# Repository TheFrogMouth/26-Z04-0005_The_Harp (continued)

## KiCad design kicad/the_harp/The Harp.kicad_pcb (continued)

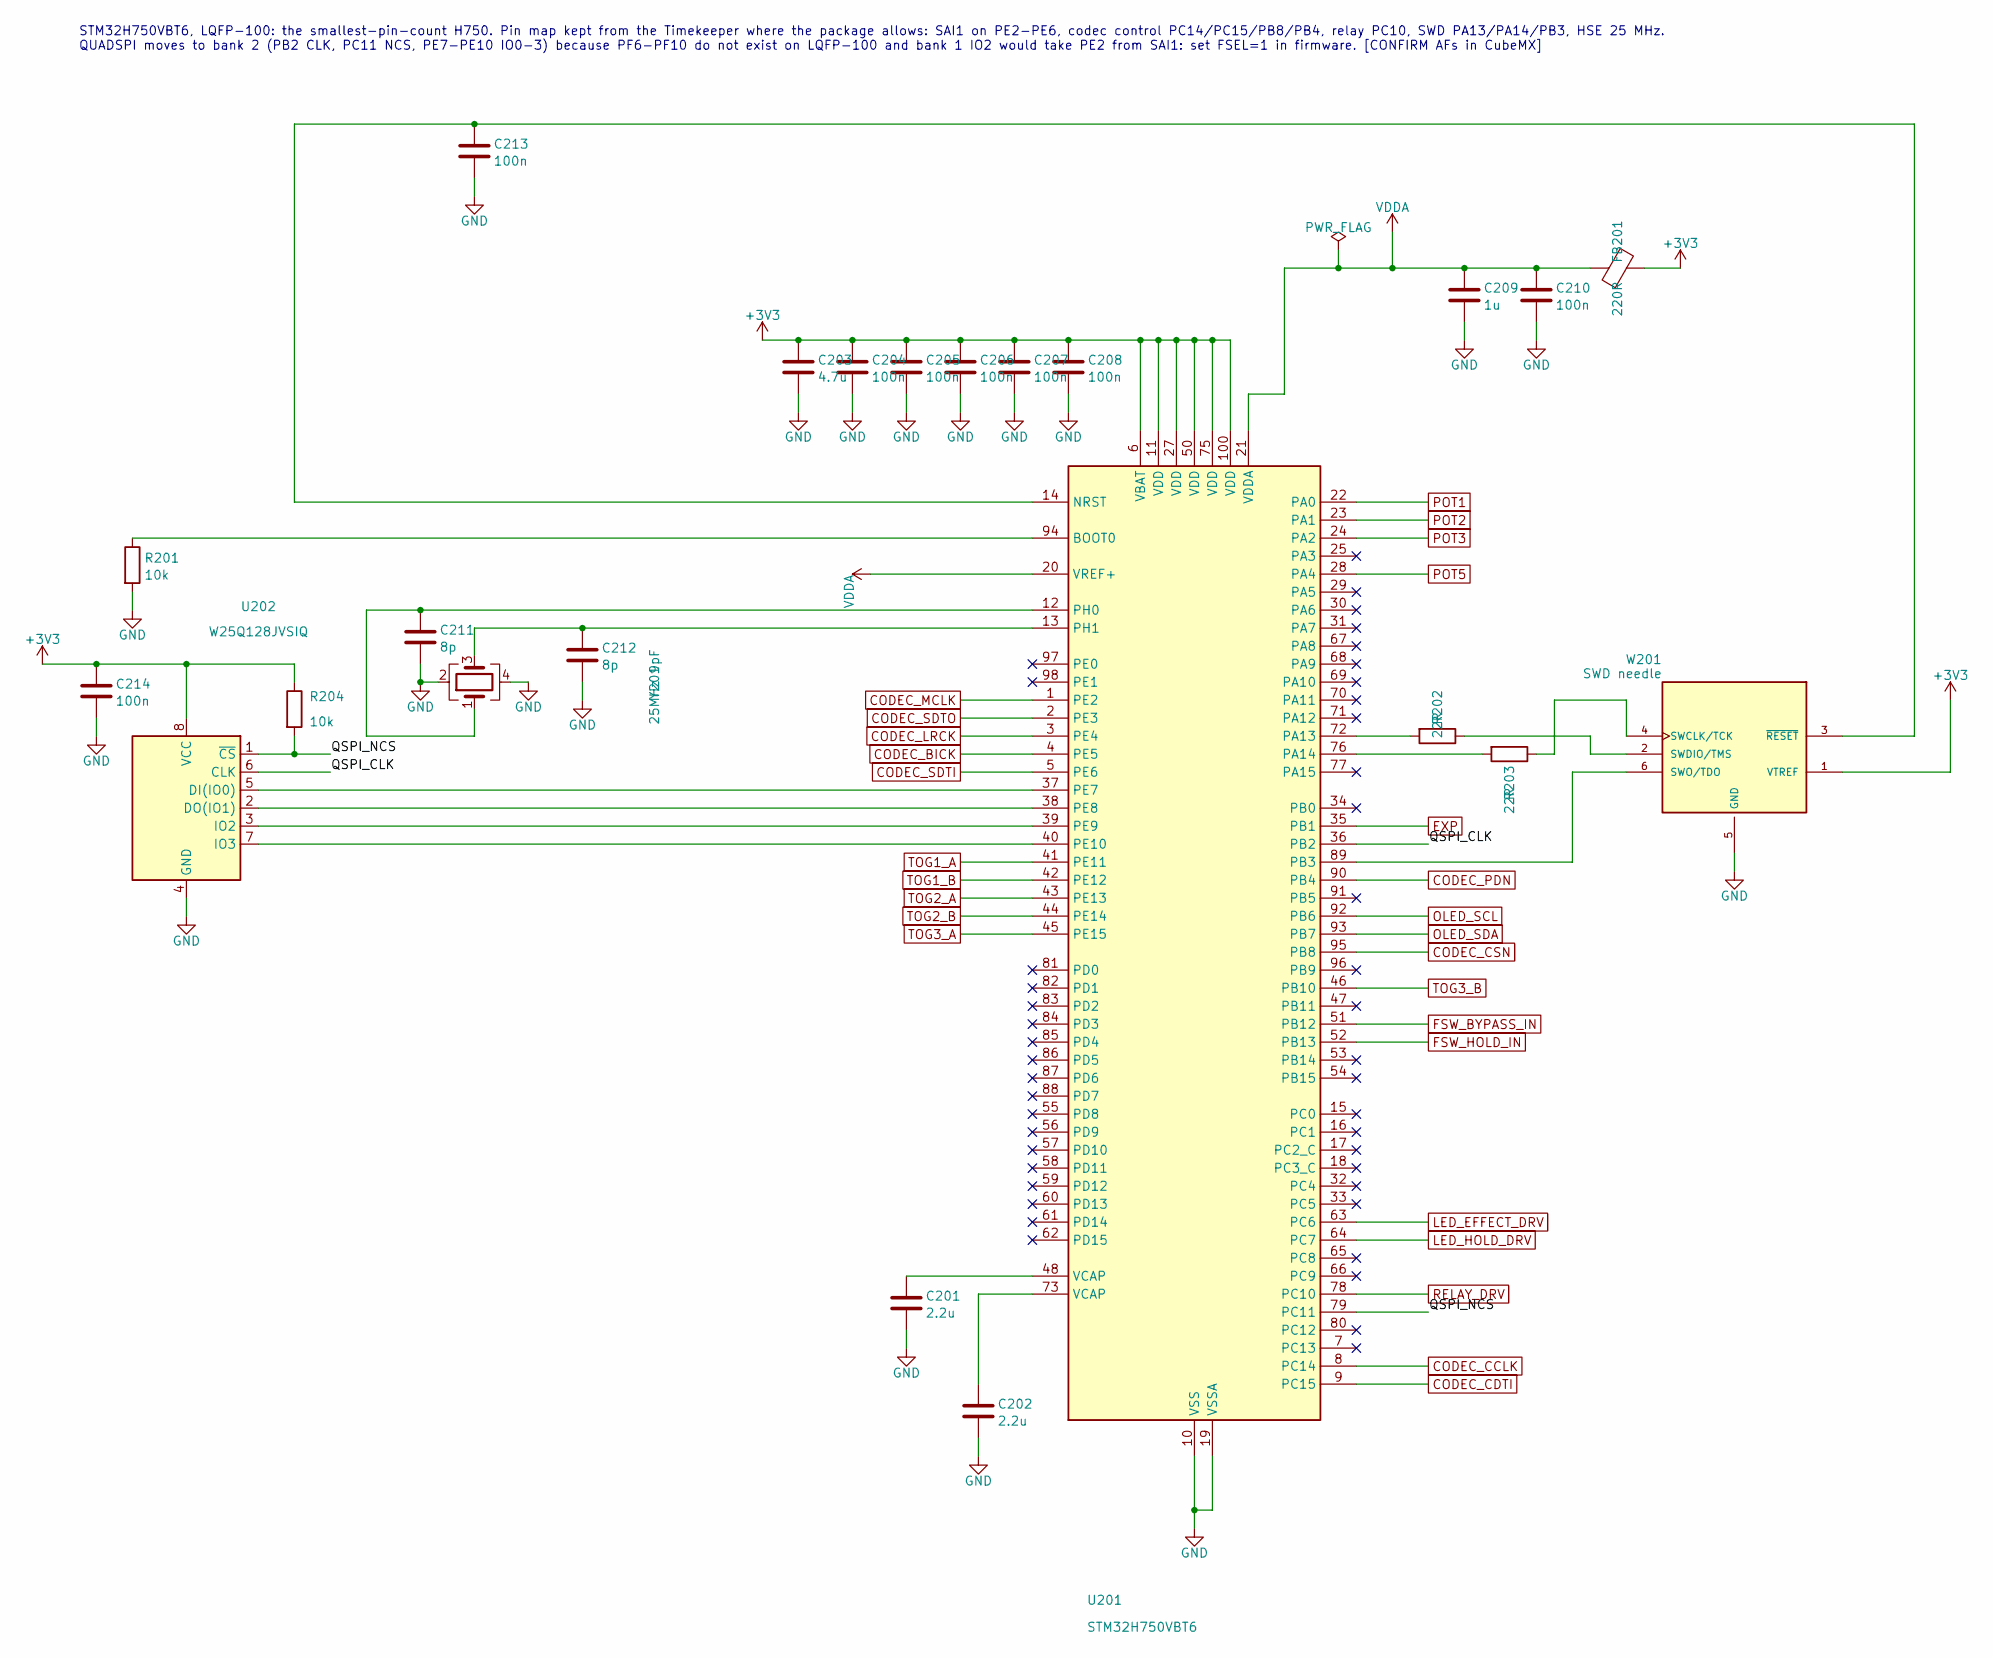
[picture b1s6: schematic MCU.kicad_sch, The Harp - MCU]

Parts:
C201, C202: 2.2u; C_0603_1608Metric
C203: 4.7u; C_0805_2012Metric
C204, C205, C206, C207, C208, C210, C213, C214: 100n; C_0603_1608Metric
C209: 1u; C_0603_1608Metric
C211, C212: 8p; C_0603_1608Metric
FB201: 220R; L_0603_1608Metric
R201, R204: 10k; R_0603_1608Metric
R202, R203: 22R; R_0603_1608Metric
U201: STM32H750VBT6; LQFP-100_14x14mm_P0.5mm; Mfg Part # STM32H750VBT6
U202: W25Q128JVSIQ; SOIC-8_5.23x5.23mm_P1.27mm; Mfg Part # W25Q128JVSIQ
W201: SWD needle; SEGGER_8.06.05_6-PIN_NEEDLE_ADAPTER
Y201: 25MHz 9pF; Crystal_SMD_2016-4Pin_2.0x1.6mm

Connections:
+3V3: C203.1, C204.1, C205.1, C206.1, C207.1, C208.1, C214.1, FB201.1, R204.1, U201.6 (VBAT), U201.11 (VDD), U201.27 (VDD), U201.50 (VDD), U201.75 (VDD), U201.100 (VDD), U202.8 (VCC), W201.1 (VTREF); also elsewhere on the board
/MCU/QSPI_CLK: U201.36 (PB2), U202.6 (CLK)
/MCU/QSPI_NCS: R204.2, U201.79 (PC11), U202.1 (~CS)
CODEC_BICK: U201.4 (PE5); also elsewhere on the board
CODEC_CCLK: U201.8 (PC14); also elsewhere on the board
CODEC_CDTI: U201.9 (PC15); also elsewhere on the board
CODEC_CSN: U201.95 (PB8); also elsewhere on the board
CODEC_LRCK: U201.3 (PE4); also elsewhere on the board
CODEC_MCLK: U201.1 (PE2); also elsewhere on the board
CODEC_PDN: U201.90 (PB4); also elsewhere on the board
CODEC_SDTI: U201.5 (PE6); also elsewhere on the board
CODEC_SDTO: U201.2 (PE3); also elsewhere on the board
EXP: U201.35 (PB1); also elsewhere on the board
FSW_BYPASS_IN: U201.51 (PB12); also elsewhere on the board
FSW_HOLD_IN: U201.52 (PB13); also elsewhere on the board
GND: C201.2, C202.2, C203.2, C204.2, C205.2, C206.2, C207.2, C208.2, C209.2, C210.2, C211.2, C212.2, C213.2, C214.2, R201.2, U201.10 (VSS), U201.19 (VSSA), U201.26 (VSS), U201.49 (VSS), U201.74 (VSS), U201.99 (VSS), U202.4 (GND), W201.5 (GND), Y201.2, Y201.4; also elsewhere on the board
LED_EFFECT_DRV: U201.63 (PC6); also elsewhere on the board
LED_HOLD_DRV: U201.64 (PC7); also elsewhere on the board
unnamed: C201.1, U201.48 (VCAP)
unnamed: C202.1, U201.73 (VCAP)
unnamed: R201.1, U201.94 (BOOT0)
unnamed: C213.1, U201.14 (NRST), W201.3 (~RESET)
unnamed: R202.2, U201.72 (PA13)
unnamed: R203.2, U201.76 (PA14)
unnamed: U201.89 (PB3), W201.6 (SWO/TDO)
unnamed: U201.37 (PE7), U202.5 (DI(IO0))
unnamed: U201.38 (PE8), U202.2 (DO(IO1))
unnamed: U201.39 (PE9), U202.3 (IO2)
unnamed: U201.40 (PE10), U202.7 (IO3)
unnamed: C211.1, U201.12 (PH0), Y201.1
unnamed: C212.1, U201.13 (PH1), Y201.3
unnamed: R203.1, W201.4 (SWCLK/TCK)
unnamed: R202.1, W201.2 (SWDIO/TMS)
OLED_SCL: U201.92 (PB6); also elsewhere on the board
OLED_SDA: U201.93 (PB7); also elsewhere on the board
POT1: U201.22 (PA0); also elsewhere on the board
POT2: U201.23 (PA1); also elsewhere on the board
POT3: U201.24 (PA2); also elsewhere on the board
POT5: U201.28 (PA4); also elsewhere on the board
RELAY_DRV: U201.78 (PC10); also elsewhere on the board
TOG1_A: U201.41 (PE11); also elsewhere on the board
TOG1_B: U201.42 (PE12); also elsewhere on the board
TOG2_A: U201.43 (PE13); also elsewhere on the board
TOG2_B: U201.44 (PE14); also elsewhere on the board
TOG3_A: U201.45 (PE15); also elsewhere on the board
TOG3_B: U201.46 (PB10); also elsewhere on the board
VDDA: C209.1, C210.1, FB201.2, U201.20 (VREF+), U201.21 (VDDA)

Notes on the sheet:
STM32H750VBT6, LQFP-100: the smallest-pin-count H750. Pin map kept from the Timekeeper where the package allows: SAI1 on PE2-PE6, codec control PC14/PC15/PB8/PB4, relay PC10, SWD PA13/PA14/PB3, HSE 25 MHz. QUADSPI moves to bank 2 (PB2 CLK, PC11 NCS, PE7-PE10 IO0-3) because PF6-PF10 do not exist on 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

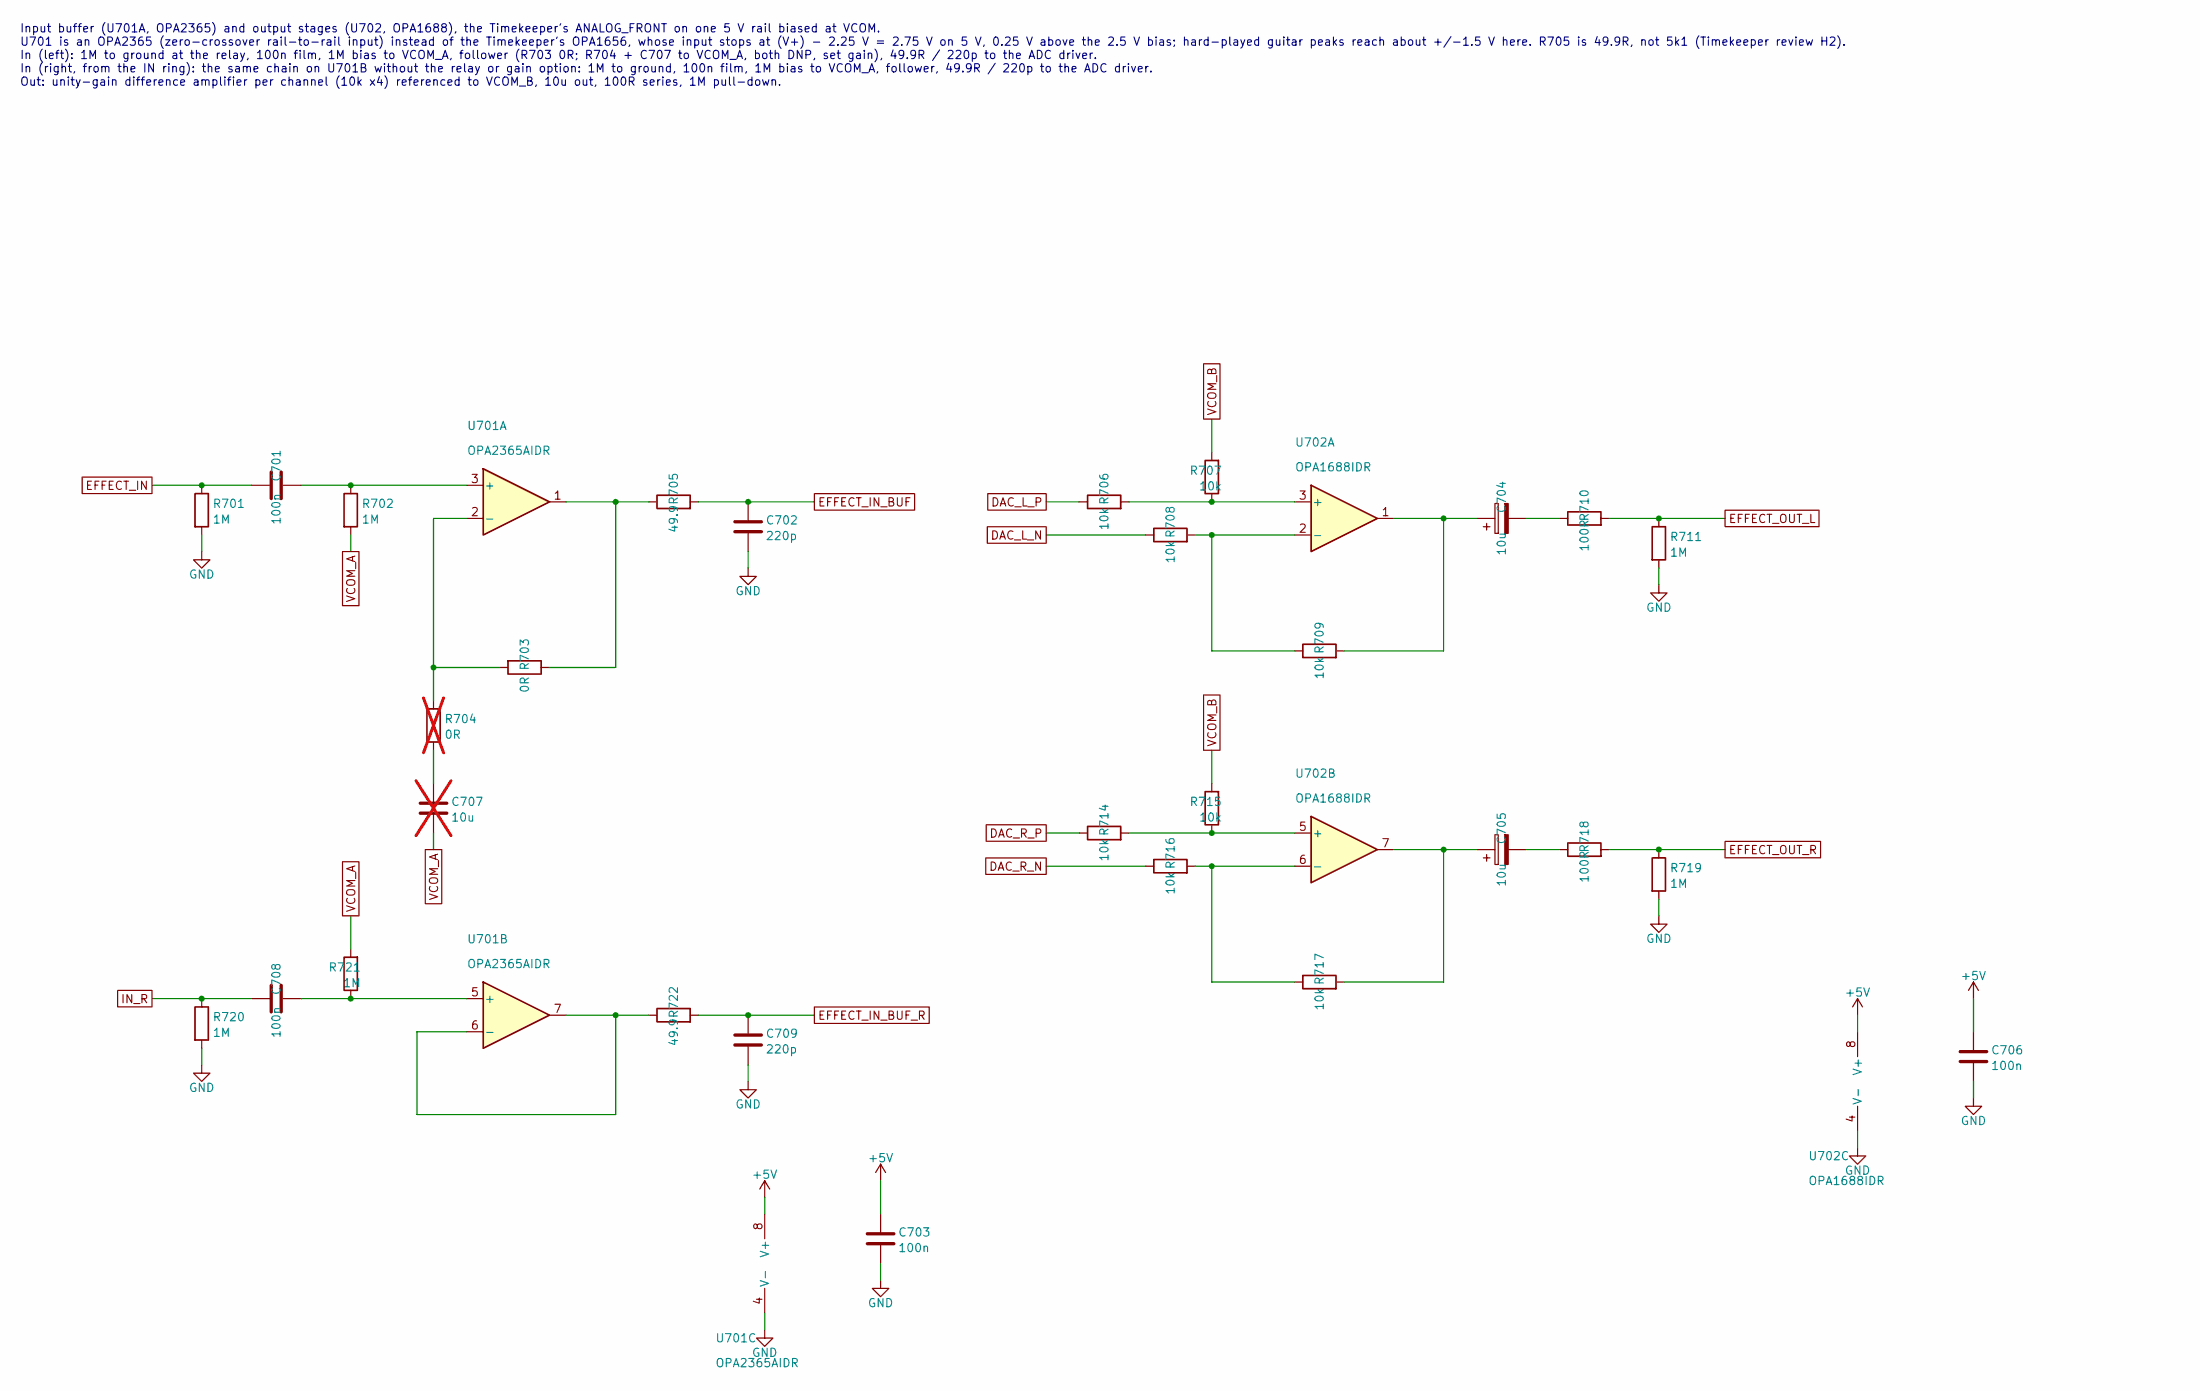
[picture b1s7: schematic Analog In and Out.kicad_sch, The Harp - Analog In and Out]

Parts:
C701, C708: 100n; C_1206_3216Metric
C702, C709: 220p; C_0603_1608Metric
C703, C706: 100n; C_0603_1608Metric
C704, C705: 10u; CP_EIA-3216-12_Kemet-S
C707: 10u; C_0805_2012Metric; not fitted
R701, R702, R711, R719, R720, R721: 1M; R_0603_1608Metric
R703: 0R; R_0603_1608Metric
R704: 0R; R_0603_1608Metric; not fitted
R705, R722: 49.9; R_0603_1608Metric
R706, R707, R708, R709, R714, R715, R716, R717: 10k; R_0603_1608Metric
R710, R718: 100R; R_0603_1608Metric
U701: OPA2365AIDR; SOIC-8_3.9x4.9mm_P1.27mm; Mfg Part # OPA2365AIDR
U702: OPA1688IDR; SOIC-8_3.9x4.9mm_P1.27mm; Mfg Part # OPA1688IDR

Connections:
+5V: C703.1, C706.1, U701.8 (V+), U702.8 (V+); also elsewhere on the board
DAC_L_N: R708.1; also elsewhere on the board
DAC_L_P: R706.1; also elsewhere on the board
DAC_R_N: R716.1; also elsewhere on the board
DAC_R_P: R714.1; also elsewhere on the board
EFFECT_IN: C701.1, R701.1; also elsewhere on the board
EFFECT_IN_BUF: C702.1, R705.2; also elsewhere on the board
EFFECT_IN_BUF_R: C709.1, R722.2; also elsewhere on the board
EFFECT_OUT_L: R710.2, R711.1; also elsewhere on the board
EFFECT_OUT_R: R718.2, R719.1; also elsewhere on the board
GND: C702.2, C703.2, C706.2, C709.2, R701.2, R711.2, R719.2, R720.2, U701.4 (V-), U702.4 (V-); also elsewhere on the board
IN_R: C708.1, R720.1; also elsewhere on the board
unnamed: C704.1, R709.2, U702.1
unnamed: C704.2, R710.1
unnamed: C705.1, R717.2, U702.7
unnamed: C705.2, R718.1
unnamed: C707.1, R704.2
unnamed: R703.1, R705.1, U701.1
unnamed: C701.2, R702.1, U701.3 (+)
unnamed: R703.2, R704.1, U701.2 (-)
unnamed: C708.2, R721.1, U701.5 (+)
unnamed: R722.1, U701.6 (-), U701.7
unnamed: R706.2, R707.1, U702.3 (+)
unnamed: R708.2, R709.1, U702.2 (-)
unnamed: R714.2, R715.1, U702.5 (+)
unnamed: R716.2, R717.1, U702.6 (-)
VCOM_A: C707.2, R702.2, R721.2; also elsewhere on the board
VCOM_B: R707.2, R715.2; also elsewhere on the board

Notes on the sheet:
Input buffer (U701A, OPA2365) and output stages (U702, OPA1688), the Timekeeper's ANALOG_FRONT on one 5 V rail biased at VCOM. U701 is an OPA2365 (zero-crossover rail-to-rail input) instead of the Timekeeper's OPA1656, whose input stops at (V+) - 2.25 V = 2.75 V on 5 V, 0.25 V above the 2.5 V bias;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

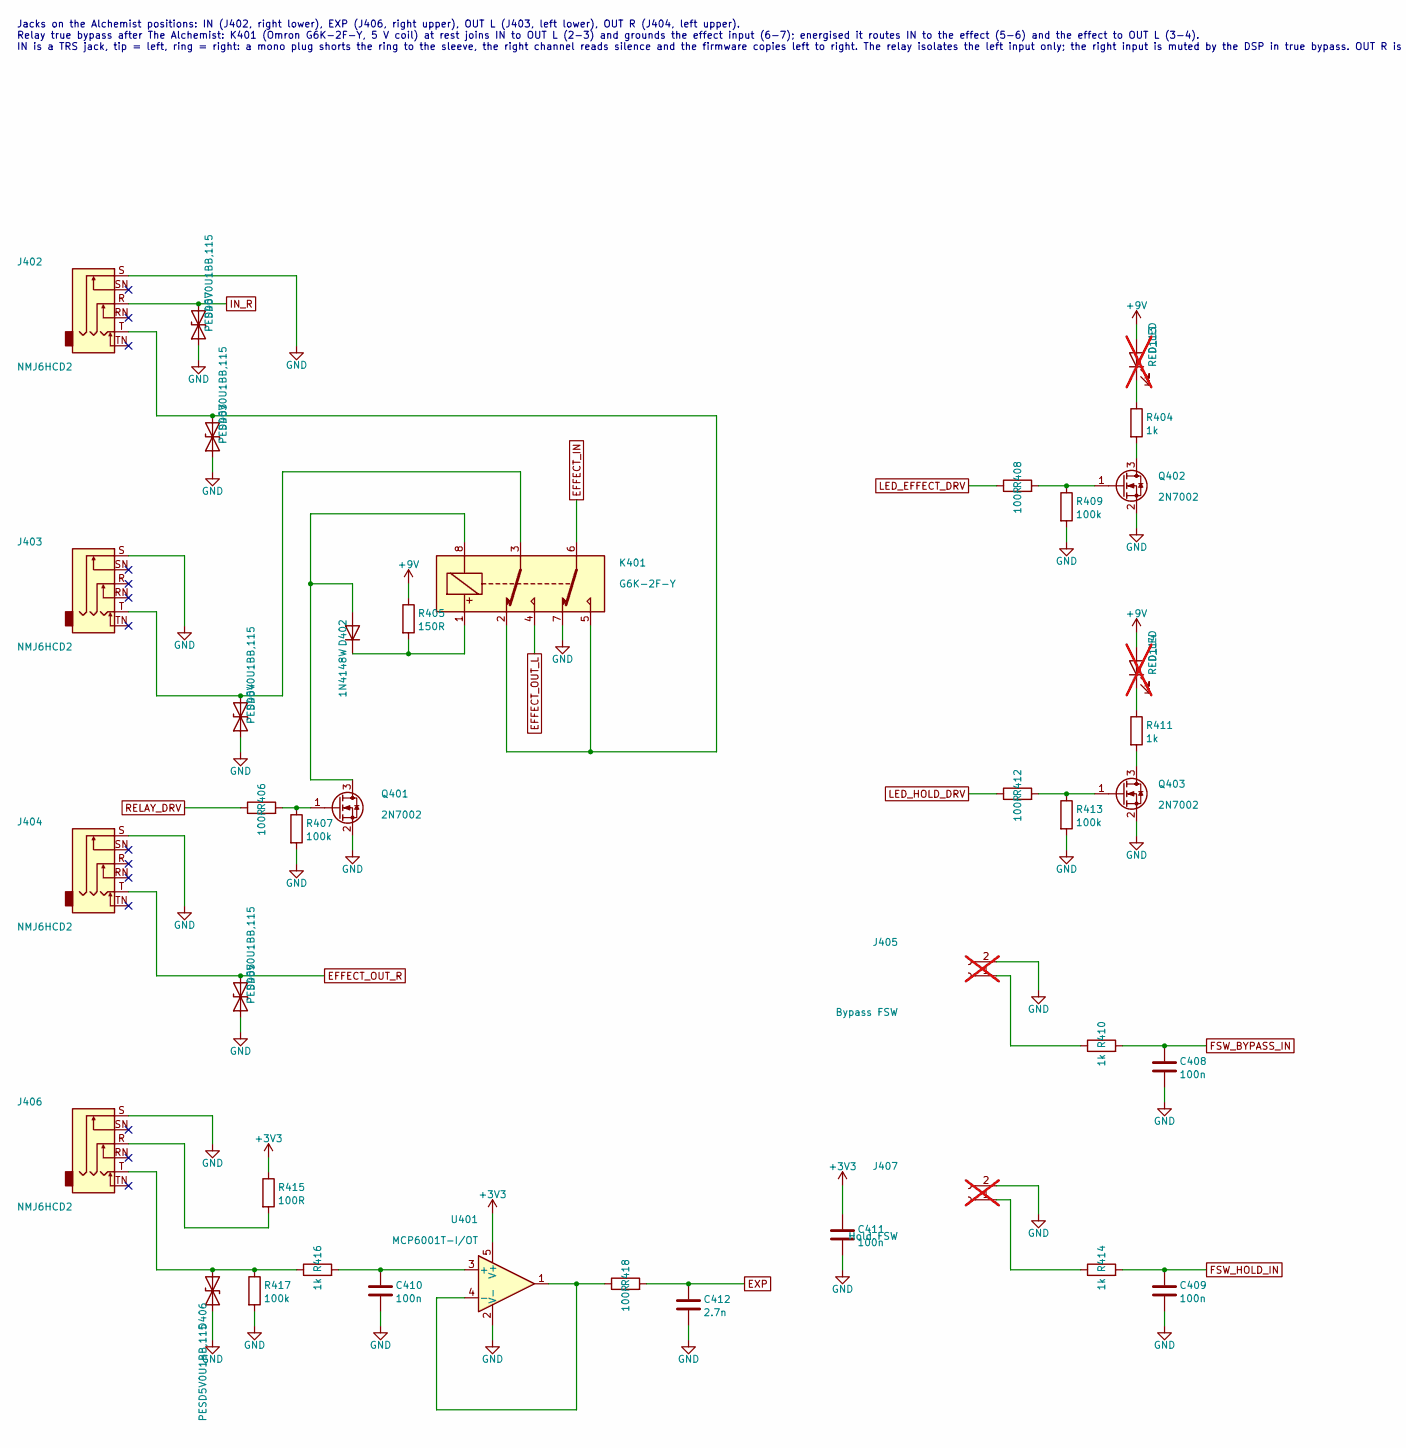
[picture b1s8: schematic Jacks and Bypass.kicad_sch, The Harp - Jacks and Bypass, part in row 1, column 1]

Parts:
C408, C409: 100n; C_0603_1608Metric; Mfg Part # CC0603KRX7R9BB104; LCSC C14663
C410, C411: 100n; C_0603_1608Metric
C412: 2.7n; C_0603_1608Metric
D113, D114: RED_LED; LED_D3.0mm; Mfg Part # WP710A10ID; not fitted
D402: 1N4148W; D_SOD-123; Mfg Part # 1N4148W-7-F; LCSC C7420318
D403, D404, D405, D406, D407: PESD5V0U1BB,115; D_SOD-523; Mfg Part # PESD5V0U1BB,115
J402, J403, J404, J406: NMJ6HCD2; Jack_6.35mm_Neutrik_NMJ6HCD2_Horizontal; Mfg Part # NMJ6HCD2; LCSC C309277
J405: Bypass FSW; R_2816_7142Metric_Pad3.20x4.45mm_HandSolder; not fitted
J407: Hold FSW; R_2816_7142Metric_Pad3.20x4.45mm_HandSolder; not fitted
K401: G6K-2F-Y; Relay_DPDT_Omron_G6K-2F-Y; Mfg Part # G6K-2F-Y DC5; LCSC C2982926
Q401, Q402, Q403: 2N7002; SOT-23; Mfg Part # 2N7002LT1G; LCSC C7420321
R404, R410, R411, R414: 1k; R_0805_2012Metric; Mfg Part # AC0805FR-071KL; LCSC C17513
R405: 150R; R_1206_3216Metric; Mfg Part # RC1206FR-07150RL; LCSC C17917
R406, R408, R412: 100R; R_0805_2012Metric; Mfg Part # AC0805FR-07100RL; LCSC C7468571
R407, R409, R413: 100k; R_0805_2012Metric; Mfg Part # AC0805FR-07100KL; LCSC C149504
R415, R418: 100R; R_0603_1608Metric
R416: 1k; R_0603_1608Metric
R417: 100k; R_0603_1608Metric
U401: MCP6001T-I/OT; SOT-23-5; Mfg Part # MCP6001T-I/OT

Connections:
+3V3: C411.1, R415.1, U401.5 (V+); also elsewhere on the board
+9V: D113.2 (A), D114.2 (A), R405.1; also elsewhere on the board
EFFECT_IN: K401.6; also elsewhere on the board
EFFECT_OUT_L: K401.4; also elsewhere on the board
EFFECT_OUT_R: D405.2 (A2), J404.T; also elsewhere on the board
EXP: C412.1, R418.2; also elsewhere on the board
FSW_BYPASS_IN: C408.1, R410.2; also elsewhere on the board
FSW_HOLD_IN: C409.1, R414.2; also elsewhere on the board
GND: C408.2, C409.2, C410.2, C411.2, C412.2, D403.1 (A1), D404.1 (A1), D405.1 (A1), D406.1 (A1), D407.1 (A1), J402.S, J403.S, J404.S, J405.2, J406.S, J407.2, K401.7, Q401.2 (S), Q402.2 (S), Q403.2 (S), R407.2, R409.2, R413.2, R417.2, U401.2 (V-); also elsewhere on the board
IN_R: D407.2 (A2), J402.R; also elsewhere on the board
LED_EFFECT_DRV: R408.1; also elsewhere on the board
LED_HOLD_DRV: R412.1; also elsewhere on the board
unnamed: D113.1 (K), R404.1
unnamed: D114.1 (K), R411.1
unnamed: D402.2 (A), K401.8, Q401.3 (D)
unnamed: D402.1 (K), K401.1, R405.2
unnamed: D403.2 (A2), J402.T, K401.2, K401.5
unnamed: D404.2 (A2), J403.T, K401.3
unnamed: D406.2 (A2), J406.T, R416.1, R417.1
unnamed: J405.1, R410.1
unnamed: J406.R, R415.2
unnamed: J407.1, R414.1
unnamed: Q401.1 (G), R406.2, R407.1
unnamed: Q402.3 (D), R404.2
unnamed: Q402.1 (G), R408.2, R409.1
unnamed: Q403.3 (D), R411.2
unnamed: Q403.1 (G), R412.2, R413.1
unnamed: C410.1, R416.2, U401.3 (+)
unnamed: R418.1, U401.1, U401.4 (-)
RELAY_DRV: R406.1; also elsewhere on the board

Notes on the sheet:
Jacks on the Alchemist positions: IN (J402, right lower), EXP (J406, right upper), OUT L (J403, left lower), OUT R (J404, left upper). Relay true bypass after The Alchemist: K401 (Omron G6K-2F-Y, 5 V coil) at rest joins IN to OUT L (2-3) and grounds the effect input (6-7); energised it routes IN to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

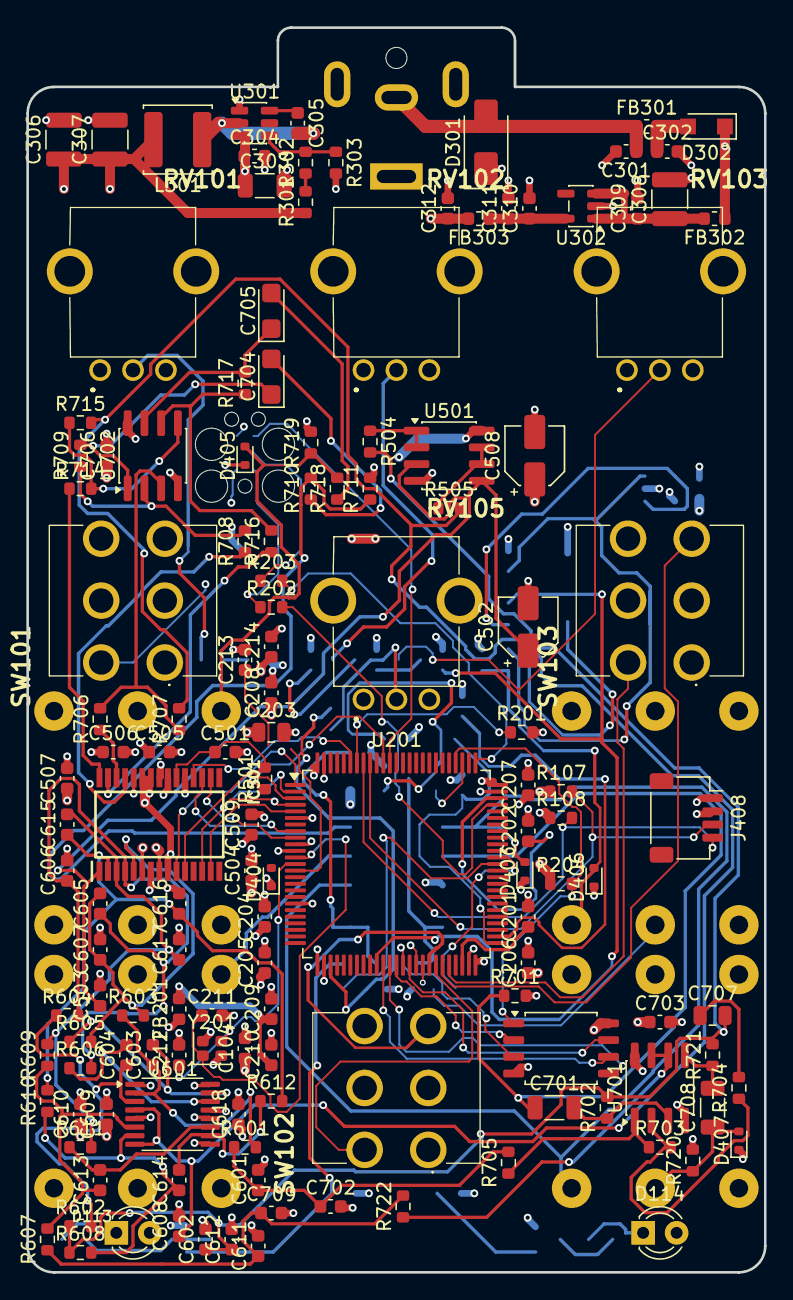
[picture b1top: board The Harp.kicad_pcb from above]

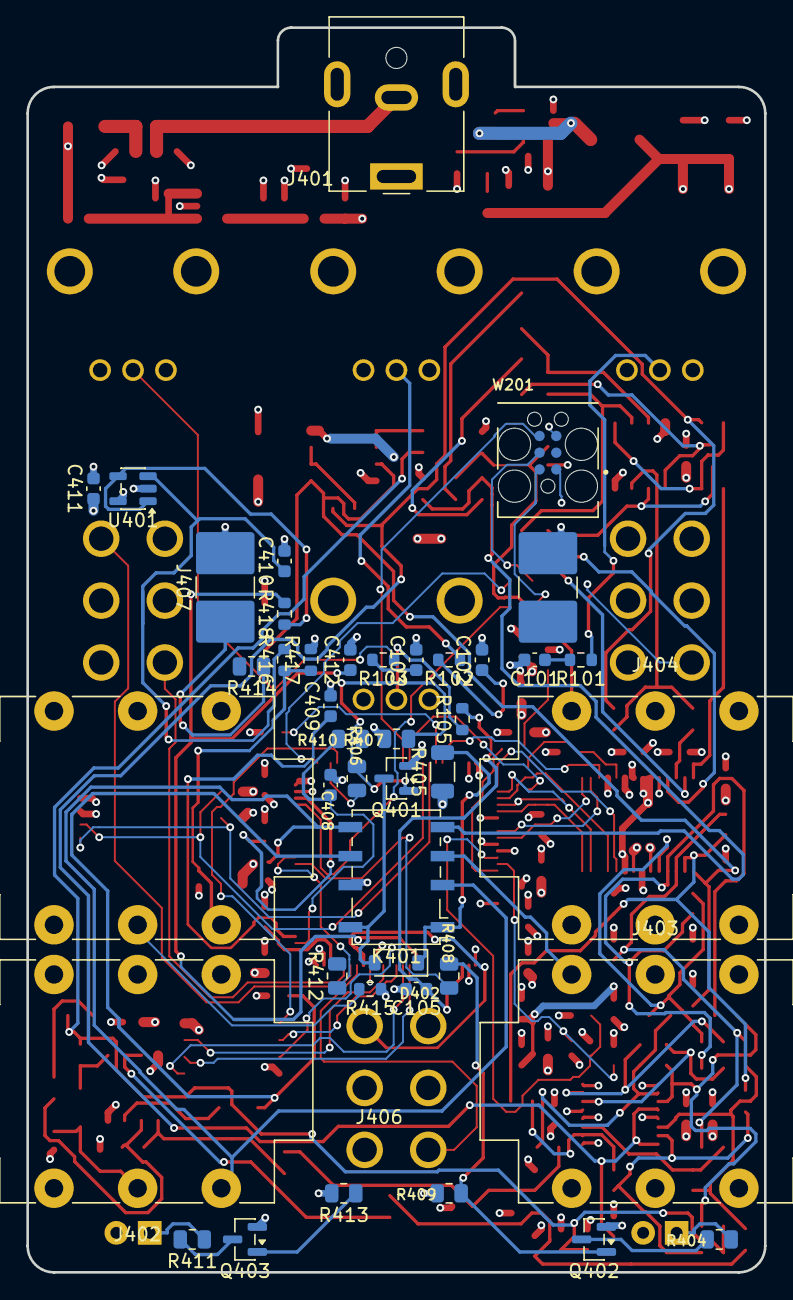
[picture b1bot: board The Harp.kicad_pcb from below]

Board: 4 copper layers, 56.0 x 94.5 mm, 181 parts (42 on the bottom side), 120 nets.

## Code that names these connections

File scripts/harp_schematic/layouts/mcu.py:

"""MCU: STM32H750VBT6 with its supplies, HSE crystal, reset and boot, SWD needle pads and the W25Q128 QSPI flash.

Two nets get local labels: QSPI_CLK (PB2, right side) and QSPI_NCS (PC11, right side) go to the flash on the
left; the flash sits on the left so its four IO lines run straight into PE7-PE10."""
from layouts.common import u, U, shunt, series

NOTES = ['C', 'Cs', 'D', 'Ds', 'E', 'F', 'Fs', 'G', 'Gs', 'A', 'As', 'B']
LEFT = {'PE2': 'CODEC_MCLK', 'PE3': 'CODEC_SDTO', 'PE4': 'CODEC_LRCK', 'PE5': 'CODEC_BICK', 'PE6': 'CODEC_SDTI',
        'PE7': None, 'PE8': None, 'PE9': None, 'PE10': None,
        'PE11': 'TOG1_A', 'PE12': 'TOG1_B', 'PE13': 'TOG2_A', 'PE14': 'TOG2_B', 'PE15': 'TOG3_A'}
RIGHT = {'PA0': 'POT1', 'PA1': 'POT2', 'PA2': 'POT3', 'PA4': 'POT5', 'PB1': 'EXP', 'PB4': 'CODEC_PDN', 'PB8': 'CODEC_CSN',
         'PB10': 'TOG3_B', 'PB6': 'OLED_SCL', 'PB7': 'OLED_SDA', 'PB12': 'FSW_BYPASS_IN', 'PB13': 'FSW_HOLD_IN', 'PC6': 'LED_EFFECT_DRV', 'PC7': 'LED_HOLD_DRV',
         'PC10': 'RELAY_DRV', 'PC14': 'CODEC_CCLK', 'PC15': 'CODEC_CDTI'}


def layout(L):
    L.allow_local = {'QSPI_CLK', 'QSPI_NCS'}
    L.text(L.sheet.notes[0], u(8), u(6))
    X, Y = u(70), u(56)
    P = L.at('U201', X, Y, ref_pos=(u(64), u(92), 'left'), val_pos=(u(64), u(93.5), 'left'))
    byname = {}
    from kisch import lib_pins
    for nb, nm, *_ in lib_pins(P.lib, P.part.unit):
        byname.setdefault(nm, []).append(nb)
    pinno = {nm: nbs[0] for nm, nbs in byname.items()}
    # ---- port pins to other sheets
    for nm, net in LEFT.items():
        if net:
            L.gl(net, ('U201', pinno[nm]), 'left', length=4 * U)
    for nm, net in RIGHT.items():
        L.gl(net, ('U201', pinno[nm]), 'right', length=4 * U)
    L.local('QSPI_CLK', ('U201', pinno['PB2']), 'right', length=4 * U)
    L.local('QSPI_NCS', ('U201', pinno['PC11']), 'right', length=4 * U)
    for nm in ['PD%d' % i for i in range(12)] + ['PE0', 'PE1', 'PD12', 'PD13', 'PD14', 'PD15', 'PA3', 'PA5', 'PA6', 'PA7', 'PA8', 'PA9', 'PA10', 'PA11', 'PA12',
               'PA15', 'PB0', 'PB5', 'PB9', 'PB11', 'PB14', 'PB15', 'PC0', 'PC1', 'PC2_C', 'PC3_C', 'PC4', 'PC5',
               'PC8', 'PC9', 'PC12', 'PC13']:
        L.nc('U201', pinno[nm])
    # ---- supplies: VDD x5 + VBAT on a +3V3 rail with six decoupling caps; VDDA through FB201 with 1u + 100n
    top = u(22)
    for nb in byname['VDD'] + byname['VBAT']:
        x, y = L.pin('U201', nb)
        L.w((x, y), (x, top))
    L.w((u(46), top), (u(72), top))
    L.pwr('+3V3', (u(46), top), 'up')
    for i, ref in enumerate(('C203', 'C204', 'C205', 'C206', 'C207', 'C208')):
        shunt(L, ref, u(48 + 3 * i), top)
    xa, ya = L.pin('U201', pinno['VDDA'])
    L.w((xa, ya), (xa, u(25)), (u(75), u(25)), (u(75), u(18)), (u(92), u(18)))          # VDDA
    L.flag((u(78), u(18)))
    L.w((u(81), u(18)), (u(81), u(16)))
    L.pwr('VDDA', (u(81), u(16)), 'up')
    shunt(L, 'C209', u(85), u(18))
    shunt(L, 'C210', u(89), u(18))
    series(L, 'FB201', u(93.5), u(18), flip=True)
    L.w(('FB201', '1'), (u(97), u(18)))
    L.pwr('+3V3', (u(97), u(18)), 'up')
    # VSS x5 (stacked) and VSSA
    xs, ys = L.pin('U201', byname['VSS'][0])
    L.w((xs, ys), (xs, u(88)))
    L.gnd((xs, u(88)))
    xsa, ysa = L.pin('U201', pinno['VSSA'])
    L.w((xsa, ysa), (xsa, u(87)), (xs, u(87)))
    # VCAP
    L.w(('U201', byname['VCAP'][0]), (u(54), u(74)))
    shunt(L, 'C201', u(54), u(74))
    L.w(('U201', byname['VCAP'][1]), (u(58), u(75)), (u(58), u(80)))
    L.at('C202', u(58), u(81.5))
    L.gnd(('C202', '2'), length=U)
    # ---- reset, boot, VREF+
    L.w(('U201', pinno['NRST']), (u(20), u(31)), (u(20), u(10)), (u(110), u(10)), (u(110), u(44)), (u(106), u(44)))
    shunt(L, 'C213', u(30), u(10))
    L.w(('U201', pinno['BOOT0']), (u(11), u(33)))
    shunt(L, 'R201', u(11), u(33))
    L.w(('U201', pinno['VREF+']), (u(52), u(35)))
    L.pwr('VDDA', (u(52), u(35)), 'left')
    # ---- HSE crystal: pin 1 (HSE_IN) below, pin 3 (HSE_OUT) above, GND pins left and right
    L.at('Y201', u(30), u(41), ang=90, ref_pos=(u(40), u(42), 'left'), val_pos=(u(40), u(43.4), 'left'))
    L.w(('U201', pinno['PH1']), (u(30), u(38)), ('Y201', '3'))                                   # HSE_OUT
    L.w(('U201', pinno['PH0']), (u(24), u(37)), (u(24), u(44)), (u(30), u(44)), ('Y201', '1'))   # HSE_IN
    shunt(L, 'C211', u(27), u(37))
    L.w(('Y201', '2'), (u(27), u(41)))
    L.w(('Y201', '4'), (u(33), u(41)))
    L.gnd((u(33), u(41)))
    shunt(L, 'C212', u(36), u(38))
    # ---- QSPI flash on the left: IO0-IO3 straight into PE7-PE10, CS and CLK by local label, 10k pull-up on CS
    L.at('U202', u(14), u(48), mirror='y', ref_pos=(u(18), u(36.8), 'center'), val_pos=(u(18), u(38.2), 'center'))
    for nm, nb in (('PE7', '5'), ('PE8', '2'), ('PE9', '3'), ('PE10', '7')):
        L.w(('U201', pinno[nm]), ('U202', nb))
    L.w(('U202', '1'), (u(22), u(45)))
    L.local('QSPI_NCS', (u(22), u(45)), 'right')
    L.w(('U202', '6'), (u(22), u(46)))
    L.local('QSPI_CLK', (u(22), u(46)), 'right')
    L.w((u(20), u(45)), (u(20), u(44)))
    L.at('R204', u(20), u(42.5), ref_pos=(u(20.8), u(41.8), 'left'), val_pos=(u(20.8), u(43.2), 'left'))
    L.w(('R204', '1'), (u(20), u(40)), (u(6), u(40)))
    L.w(('U202', '8'), (u(14), u(40)))
    L.pwr('+3V3', (u(6), u(40)), 'up')
    shunt(L, 'C214', u(9), u(40))
    L.gnd(('U202', '4'), length=U)
    # ---- SWD needle pads on the right: SWDIO / SWCLK through 22R, SWO, NRST, +3V3, GND
    L.at('W201', u(100), u(46), mirror='y')
    L.w(('U201', pinno['PA13']), (u(82), u(44)))
    series(L, 'R202', u(83.5), u(44), flip=True, ref_pos=(u(83.5), u(42.4), 'center'), val_pos=(u(83.5), u(43.4), 'center'))
    L.w(('R202', '1'), (u(92), u(44)), (u(92), u(45)), ('W201', '2'))
    L.w(('U201', pinno['PA14']), (u(86), u(45)))
    series(L, 'R203', u(87.5), u(45), flip=True, ref_pos=(u(87.5), u(46.6), 'center'), val_pos=(u(87.5), u(47.6), 'center'))
    L.w(('R203', '1'), (u(90), u(45)), (u(90), u(42)), (u(94), u(42)), ('W201', '4'))
    L.w(('U201', pinno['PB3']), (u(91), u(51)), (u(91), u(46)), ('W201', '6'))
    L.w(('W201', '1'), (u(112), u(46)), (u(112), u(42)))
    L.pwr('+3V3', (u(112), u(42)), 'up')
    L.gnd(('W201', '5'), length=U)

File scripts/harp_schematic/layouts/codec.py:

"""Codec: AK4621EF, its supplies and VCOM, the two OPA2348 VCOM buffers."""
from layouts.common import u, U, shunt, series


def layout(L):
    L.text(L.sheet.notes[0], u(8), u(6))
    X, Y = 56, 24
    L.at('IC501', u(X), u(Y), ref_pos=(u(44), u(24), 'left'), val_pos=(u(44), u(25.5), 'left'))
    # ---- digital interface, left side, from the MCU
    L.w(('IC501', '9'), (u(52), u(30)), (u(52), u(18)))                        # P/S high
    for pin, net in (('10', 'CODEC_MCLK'), ('11', 'CODEC_LRCK'), ('12', 'CODEC_BICK'), ('13', 'CODEC_SDTO'), ('14', 'CODEC_SDTI')):
        L.gl(net, ('IC501', pin), 'left', length=8 * U)
    L.nc('IC501', '15')
    # ---- +3V3: TVDD, DVDD, P/S, three 100n
    L.w(('IC501', '25'), (u(59.5), u(18)))
    L.w(('IC501', '24'), (u(62.5), u(18)))
    L.w((u(40), u(18)), (u(62.5), u(18)))
    L.pwr('+3V3', (u(40), u(18)), 'up')
    for ref, x in (('C504', 42), ('C505', 45), ('C506', 48)):
        shunt(L, ref, u(x), u(18))
    # ---- +5V: AVDD, VREF, 100n + 10u
    L.w(('IC501', '6'), (u(65), u(16)))
    L.w(('IC501', '8'), (u(66), u(16)))
    L.w((u(65), u(16)), (u(80), u(16)))
    L.pwr('+5V', (u(80), u(16)), 'up')
    shunt(L, 'C507', u(72), u(16))
    shunt(L, 'C508', u(76), u(16))
    # ---- DAC outputs to the output stages
    for pin, net in (('30', 'DAC_R_P'), ('29', 'DAC_R_N'), ('28', 'DAC_L_P'), ('27', 'DAC_L_N')):
        L.gl(net, ('IC501', pin), 'right', length=8 * U)
    # ---- mode pins: SDFIL, DEM0 and DFS0 low; PDN from the MCU through 5k1 with 100n
    L.w(('IC501', '23'), (u(76), u(29.5)), (u(76), u(28.5)), (u(88), u(28.5)))
    L.w(('IC501', '22'), (u(76), u(30.5)), (u(76), u(29.5)))
    L.gnd((u(88), u(28.5)))
    L.w(('IC501', '21'), (u(99), u(31.5)))                                     # PDN
    shunt(L, 'C501', u(96), u(31.5))
    series(L, 'R501', u(100.5), u(31.5), flip=True)
    L.w(('R501', '1'), (u(104), u(31.5)))
    L.gl('CODEC_PDN', (u(104), u(31.5)), 'right')
    L.w(('IC501', '20'), (u(92), u(32.5)), (u(92), u(36)))
    L.gnd((u(92), u(36)))
    for pin, net in (('19', 'CODEC_CSN'), ('18', 'CODEC_CCLK'), ('17', 'CODEC_CDTI')):
        L.gl(net, ('IC501', pin), 'right', length=8 * U)
    L.nc('IC501', '16')
    # ---- analogue inputs: AINL and AINR from the ADC driver channels
    L.gl('ADC_R_P', ('IC501', '2'), 'right', length=8 * U)
    L.gl('ADC_R_N', ('IC501', '3'), 'right', length=8 * U)
    L.gl('ADC_L_P', ('IC501', '4'), 'right', length=8 * U)
    L.gl('ADC_L_N', ('IC501', '5'), 'right', length=8 * U)
    # ---- ground and VCOM
    L.w(('IC501', '7'), (u(62), u(46)), (u(58), u(46)), (u(58), u(49)))
    L.w(('IC501', '26'), (u(64), u(46)), (u(62), u(46)))
    L.gnd((u(58), u(49)))
    L.w(('IC501', '1'), (u(67), u(48)), (u(77), u(48)))                        # VCOM bus
    shunt(L, 'C502', u(69), u(48))
    shunt(L, 'C503', u(73), u(48))
    # ---- VCOM buffers: U501A -> VCOM_A, U501B -> VCOM_B
    for unit, Yc, riser, pp, nn, oo, res, net in ((1, 62, 77, '3', '2', '1', 'R504', 'VCOM_A'), (2, 84, 74, '5', '6', '7', 'R505', 'VCOM_B')):
        L.at('U501', u(80), u(Yc), unit=unit, ref_pos=(u(78), u(Yc - 2.6), 'left'), val_pos=(u(78), u(Yc + 2.6), 'left'))
        L.w((u(riser), u(48)), (u(riser), u(Yc - 1)), ('U501', pp, unit))
        L.w(('U501', oo, unit), (u(90), u(Yc)), (u(90), u(Yc + 11)), (u(75), u(Yc + 11)), (u(75), u(Yc + 1)), ('U501', nn, unit))
        L.pwr('+5V', ('U501', '8', unit), 'up', length=U)
        L.gnd(('U501', '4', unit), length=U)
        L.w((u(90), u(Yc)), (u(92), u(Yc)))
        series(L, res, u(93.5), u(Yc))
        L.w((res, '2'), (u(97), u(Yc)))
        L.gl(net, (u(97), u(Yc)), 'right')
    L.pwr('+5V', (u(104), u(66)), 'up')
    L.w((u(104), u(66)), (u(104), u(68)))
    shunt(L, 'C509', u(104), u(68))

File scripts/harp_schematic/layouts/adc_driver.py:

"""ADC Driver: THS4522 channel A (left) and B (right) as single-ended to differential drivers into the AK4621 inputs."""
from layouts.common import u, U, shunt, series

# ref and pin names per channel (the two units of U601 have identical pin positions)
CH = {
    'A': dict(unit=1, in_net='EFFECT_IN_BUF', out='ADC_L', dy=0, pin={'PD': '1', 'INP': '2', 'INN': '3', 'VOCM': '4', 'VCC': '13', 'OUTP': '14', 'OUTN': '15', 'VSS': '16'},
              ref=dict(C601='C601', C602='C602', R601='R601', R602='R602', R603='R603', R604='R604', R605='R605', R606='R606',
                       C603='C603', C604='C604', C605='C605', C606='C606', C607='C607', C608='C608')),
    'B': dict(unit=2, in_net='EFFECT_IN_BUF_R', out='ADC_R', dy=48, pin={'PD': '5', 'INP': '6', 'INN': '7', 'VOCM': '8', 'VCC': '9', 'OUTP': '10', 'OUTN': '11', 'VSS': '12'},
              ref=dict(C601='C611', C602='C612', R601='R607', R602='R608', R603='R609', R604='R610', R605='R611', R606='R612',
                       C603='C613', C604='C614', C605='C615', C606='C616', C607='C617', C608=None)),
}


def channel(L, ch):
    c = CH[ch]
    un, dy, P, R = c['unit'], c['dy'], c['pin'], c['ref']
    Y = lambda n: u(n + dy)
    pn = lambda k: ('U601', P[k], un)
    X = u(60)
    L.at('U601', X, Y(40), unit=un, ref_pos=(u(50), Y(46.5), 'left'), val_pos=(u(50), Y(48), 'left'))
    # ---- inputs: input buffer (top) and VCOM_A reference (bottom)
    for y, net, cap, res, pin in ((34, c['in_net'], R['C601'], R['R601'], 'INP'), (46, 'VCOM_A', R['C602'], R['R602'], 'INN')):
        L.gl(net, (u(26), Y(y)), 'left')
        L.w((u(26), Y(y)), (u(34), Y(y)))
        shunt(L, cap, u(30), Y(y))
        series(L, res, u(35.5), Y(y))
        L.w((res, '2'), (u(50), Y(y)), 'V', pn(pin))
    # ---- outputs through 40.2R to ADC_x_N (top) / ADC_x_P (bottom)
    L.w(pn('OUTN'), (u(71), Y(38)))
    series(L, R['R605'], u(72.5), Y(38))
    L.w((R['R605'], '2'), (u(90), Y(38)))
    L.w(pn('OUTP'), (u(71), Y(42)))
    series(L, R['R606'], u(72.5), Y(42))
    L.w((R['R606'], '2'), (u(86), Y(42)))
    L.at(R['C605'], u(80), Y(40), ang=180)                          # across ADC_P (pin 1, below) / ADC_N
    L.w((u(80), Y(38)), (R['C605'], '2'))
    L.w((R['C605'], '1'), (u(80), Y(42)))
    shunt(L, R['C606'], u(83), Y(42))
    L.gl(c['out'] + '_P', (u(86), Y(42)), 'right')
    shunt(L, R['C607'], u(92), Y(38))
    L.w((u(90), Y(38)), (u(96), Y(38)))
    L.gl(c['out'] + '_N', (u(96), Y(38)), 'right')
    # ---- feedback: C603 / C604 to the outputs, R603 / R604 to the filtered outputs
    L.w((u(44), Y(34)), (u(44), Y(23)), (u(53), Y(23)))
    series(L, R['C603'], u(54.5), Y(23))
    L.w((R['C603'], '2'), (u(69), Y(23)), (u(69), Y(38)))
    L.w((u(40), Y(34)), (u(40), Y(19)), (u(60), Y(19)))
    series(L, R['R603'], u(61.5), Y(19))
    L.w((R['R603'], '2'), (u(78), Y(19)), (u(78), Y(38)))
    L.w((u(44), Y(46)), (u(44), Y(59)), (u(53), Y(59)))
    series(L, R['C604'], u(54.5), Y(59))
    L.w((R['C604'], '2'), (u(69), Y(59)), (u(69), Y(42)))
    L.w((u(40), Y(46)), (u(40), Y(63)), (u(60), Y(63)))
    series(L, R['R604'], u(61.5), Y(63))
    L.w((R['R604'], '2'), (u(78), Y(63)), (u(78), Y(42)))
    # ---- supply and VOCM
    L.w(pn('VCC'), (u(58.5), Y(29)))
    L.pwr('+5V', (u(58.5), Y(29)), 'up')
    L.w(pn('PD'), (u(60), Y(31)), (u(58.5), Y(31)))
    L.gnd(pn('VSS'), length=U)
    L.w(pn('VOCM'), (u(60), Y(51)), (u(53), Y(51)))
    if R['C608']:
        shunt(L, R['C608'], u(57), Y(51))
    L.gl('VCOM_B', (u(53), Y(51)), 'left')


def layout(L):
    L.text(L.sheet.notes[0], u(8), u(6))
    channel(L, 'A')
    channel(L, 'B')
    # ---- supply decoupling
    L.pwr('+5V', (u(90), u(22)), 'up')
    L.w((u(90), u(22)), (u(90), u(24)), (u(96), u(24)))
    shunt(L, 'C609', u(92), u(24))
    shunt(L, 'C610', u(96), u(24))
    L.pwr('+5V', (u(90), u(70)), 'up')
    L.w((u(90), u(70)), (u(90), u(72)), (u(92), u(72)))
    shunt(L, 'C618', u(92), u(72))
